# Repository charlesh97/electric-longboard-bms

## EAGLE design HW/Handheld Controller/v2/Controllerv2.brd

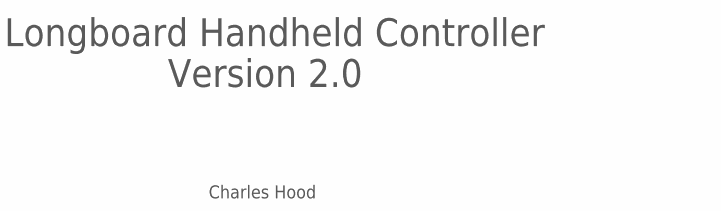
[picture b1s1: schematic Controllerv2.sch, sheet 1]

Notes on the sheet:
Longboard Handheld Controller
Version 2.0
Charles Hood

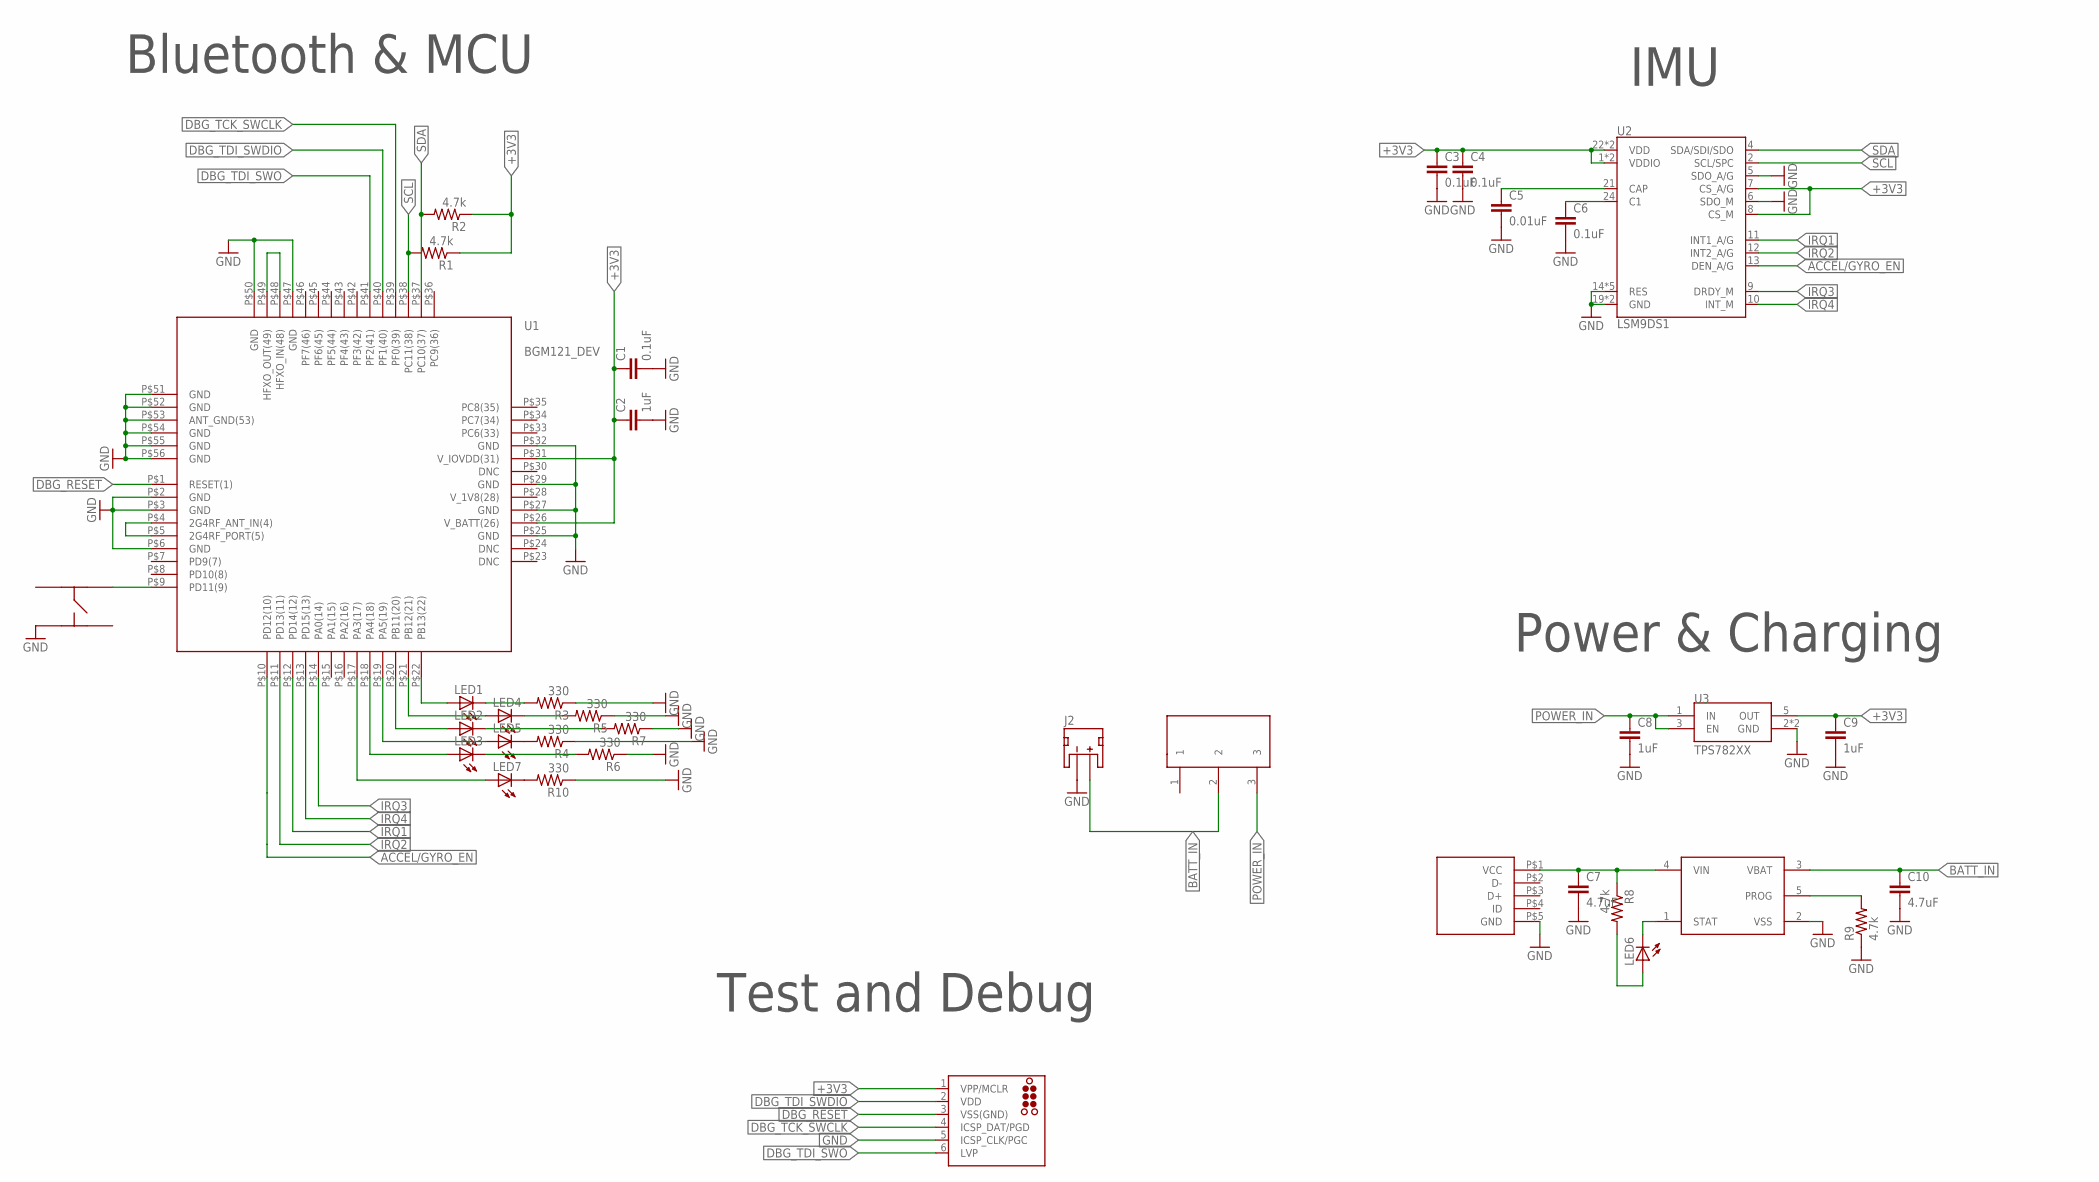
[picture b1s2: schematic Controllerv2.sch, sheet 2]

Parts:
C1, C3, C4, C6: 0.1uF; C0201
C2, C8, C9: 1uF; C0201
C5: 0.01uF; C0201
C7, C10: 4.7uF; C0402
J1: MICRO_USB; MOLEX_USB
J2: JST_2MM_MALE; JST-2-SMD
J3: TC2030-MCP-NL
LED1, LED2, LED3, LED4, LED5, LED6, LED7: LEDCHIP-LED0603; CHIP-LED0603
R1, R2, R8, R9: 4.7k; R0201
R3, R4, R5, R6, R7, R10: 330; R0201
S1: KMR731NG
U1: BGM121_DEV; BGM121_PAC
U2: LSM9DS1; LGA24-8X4
U3: TPS782XX; SOT23-5L
U4: MCP73831; SOT23-5L
U$1: SPDT_THRU

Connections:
+3V3: C1.1, C2.1, C3.1, C4.1, C9.1, J3.1 (VPP/MCLR), R1.1, R2.1, U1.P$26 (V_BATT(26)), U1.P$31 (V_IOVDD(31)), U2.1 (VDDIO), U2.3 (VDDIO), U2.7 (CS_A/G), U2.8 (CS_M), U2.22 (VDD), U2.23 (VDD), U3.5 (OUT)
ACCEL/GYRO_EN: U1.P$10 (PD12(10)), U2.13 (DEN_A/G)
BATT_IN: C10.1, J2.2 (+), U4.3 (VBAT), U$1.2
DBG_RESET: J3.3 (VSS(GND)), U1.P$1 (RESET(1))
DBG_TCK_SWCLK: J3.4 (ICSP_DAT/PGD), U1.P$39 (PF0(39))
DBG_TDI_SWDIO: J3.2 (VDD), U1.P$40 (PF1(40))
DBG_TDI_SWO: J3.6 (LVP), U1.P$41 (PF2(41))
GND: C1.2, C2.2, C3.2, C4.2, C5.2, C6.2, C7.2, C8.2, C9.2, C10.2, J1.P$5 (GND), J2.1 (-), J3.5 (ICSP_CLK/PGC), R3.1, R4.1, R5.1, R6.1, R7.1, R9.1, R10.1, S1.P$4, U1.P$2 (GND), U1.P$3 (GND), U1.P$6 (GND), U1.P$25 (GND), U1.P$27 (GND), U1.P$29 (GND), U1.P$32 (GND), U1.P$47 (GND), U1.P$50 (GND), U1.P$51 (GND), U1.P$52 (GND), U1.P$53 (ANT_GND(53)), U1.P$54 (GND), U1.P$55 (GND), U1.P$56 (GND), U2.5 (SDO_A/G), U2.6 (SDO_M), U2.14 (RES), U2.15 (RES), U2.16 (RES), U2.17 (RES), U2.18 (RES), U2.19 (GND), U2.20 (GND), U3.2 (GND), U3.4 (GND), U4.2 (VSS)
IRQ1: U1.P$12 (PD14(12)), U2.11 (INT1_A/G)
IRQ2: U1.P$11 (PD13(11)), U2.12 (INT2_A/G)
IRQ3: U1.P$14 (PA0(14)), U2.9 (DRDY_M)
IRQ4: U1.P$13 (PD15(13)), U2.10 (INT_M)
unnamed: LED1.A, U1.P$22 (PB13(22))
unnamed: LED4.A, U1.P$21 (PB12(21))
unnamed: LED2.A, U1.P$20 (PB11(20))
unnamed: LED5.A, U1.P$19 (PA5(19))
unnamed: LED3.C, R6.2
unnamed: LED3.A, U1.P$18 (PA4(18))
unnamed: C5.1, U2.21 (CAP)
unnamed: C6.1, U2.24 (C1)
unnamed: C7.1, J1.P$1 (VCC), R8.1, U4.4 (VIN)
unnamed: R9.2, U4.5 (PROG)
unnamed: LED6.A, R8.2
unnamed: LED6.C, U4.1 (STAT)
unnamed: S1.P$2, U1.P$9 (PD11(9))
unnamed: LED7.C, R10.2
unnamed: LED7.A, U1.P$17 (PA3(17))
unnamed: LED4.C, R5.2
unnamed: LED2.C, R7.2
unnamed: LED5.C, R4.2
unnamed: U1.P$4 (2G4RF_ANT_IN(4)), U1.P$5 (2G4RF_PORT(5))
unnamed: LED1.C, R3.2
unnamed: U1.P$48 (HFXO_IN(48)), U1.P$49 (HFXO_OUT(49))
POWER_IN: C8.1, U3.1 (IN), U3.3 (EN), U$1.3
SCL: R1.2, U1.P$38 (PC11(38)), U2.2 (SCL/SPC)
SDA: R2.2, U1.P$37 (PC10(37)), U2.4 (SDA/SDI/SDO)
V_1V8(28): U1.P$28 (V_1V8(28))

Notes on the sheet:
Bluetooth & MCU
IMU
Power & Charging
Test and Debug

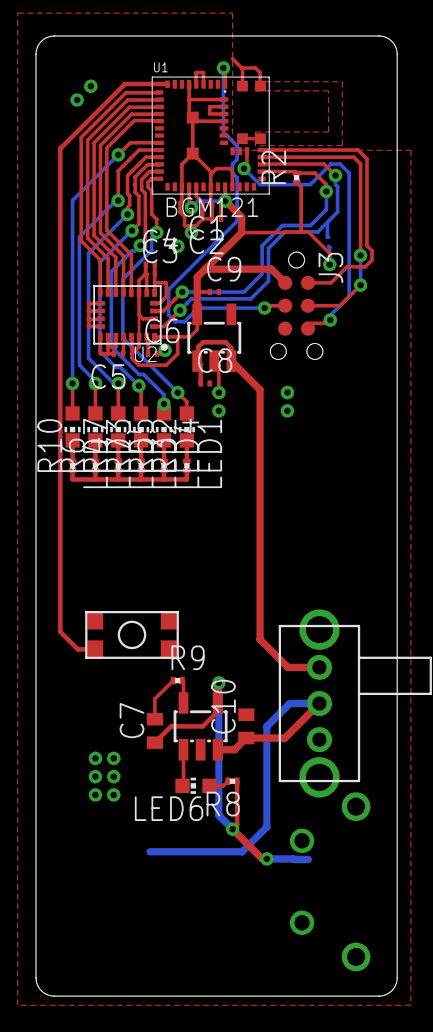
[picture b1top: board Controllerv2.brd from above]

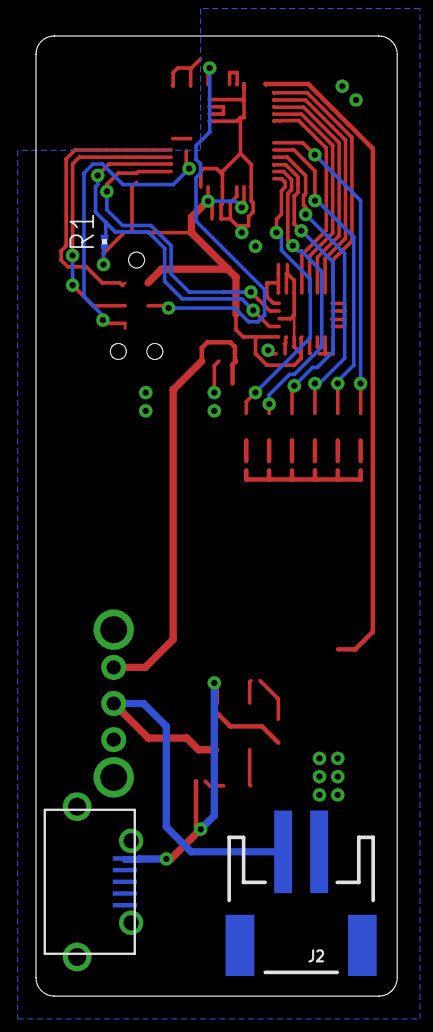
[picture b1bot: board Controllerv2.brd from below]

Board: 2 copper layers, 20.1 x 53.3 mm, 36 parts (3 on the bottom side), 36 nets.

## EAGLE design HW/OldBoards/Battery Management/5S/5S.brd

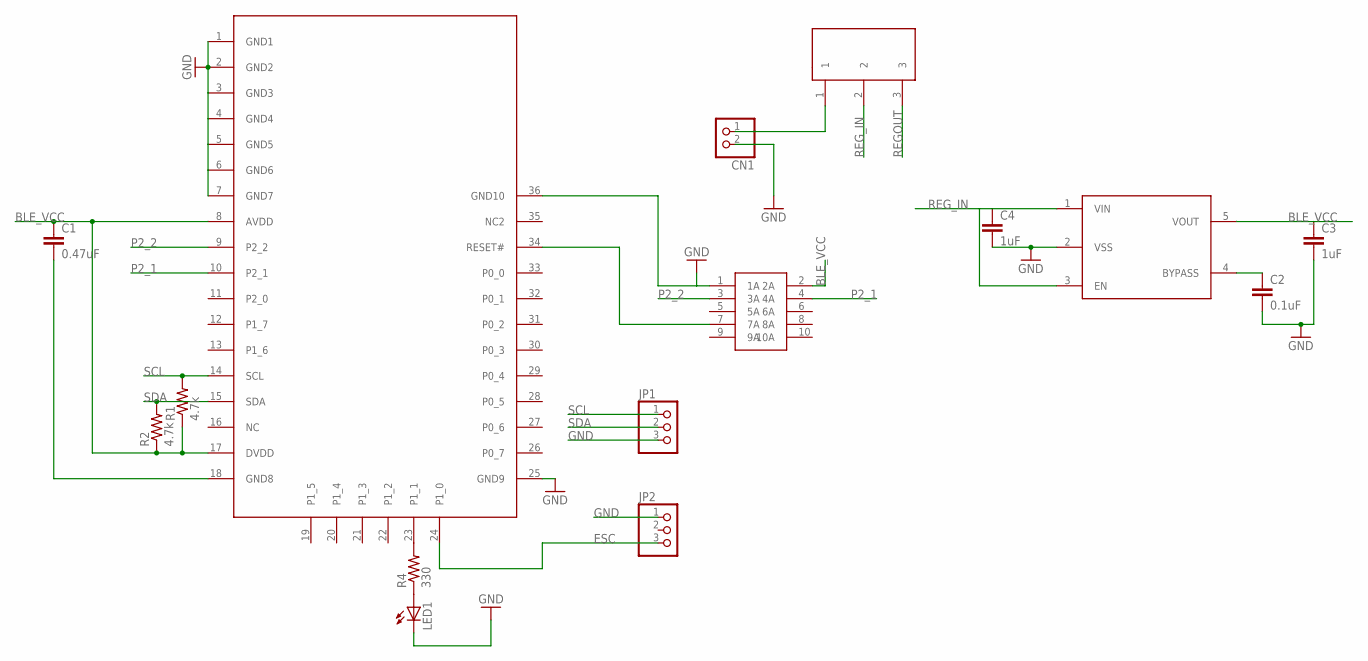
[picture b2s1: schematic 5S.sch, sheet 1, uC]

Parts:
C1: 0.47uF; C0402
C2: 0.1uF; C0402
C3, C4: 1uF; C0402
CN1: JST_2PIN-THM; JST-PH-2-THM
JP1, JP2: PINHD-1X3; 1X03
LED1: LEDCHIP-LED0805; CHIP-LED0805
R1, R2: 4.7k; R0402
R4: 330; R0402
U$1: BLE113; BLUEGIGA
U$2: RIBBON_10POS_MALE
U$4: SPDT_THRU
U$5: LP3985; SOT23-5L

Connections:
BLE_VCC: C1.1, C3.1, R1.1, R2.1, U$1.8 (AVDD), U$1.17 (DVDD), U$2.2 (2A), U$5.5 (VOUT)
ESC: JP2.3, U$1.24 (P1_0)
GND: C2.2, C3.2, C4.2, CN1.2 (1), JP1.3, JP2.1, LED1.C, U$1.1 (GND1), U$1.2 (GND2), U$1.3 (GND3), U$1.4 (GND4), U$1.5 (GND5), U$1.6 (GND6), U$1.7 (GND7), U$1.25 (GND9), U$1.36 (GND10), U$2.1 (1A), U$5.2 (VSS); also elsewhere on the board
unnamed: U$1.34 (RESET#), U$2.7 (7A)
unnamed: CN1.1 (2), U$4.1
unnamed: C1.2, U$1.18 (GND8)
unnamed: R4.2, U$1.23 (P1_1)
unnamed: C2.1, U$5.4 (BYPASS)
unnamed: LED1.A, R4.1
P2_1: U$1.10 (P2_1), U$2.4 (4A)
P2_2: U$1.9 (P2_2), U$2.3 (3A)
REGOUT: U$4.3; also elsewhere on the board
REG_IN: C4.1, U$4.2, U$5.1 (VIN), U$5.3 (EN)
SCL: JP1.1, R1.2, U$1.14 (SCL); also elsewhere on the board
SDA: JP1.2, R2.2, U$1.15 (SDA); also elsewhere on the board

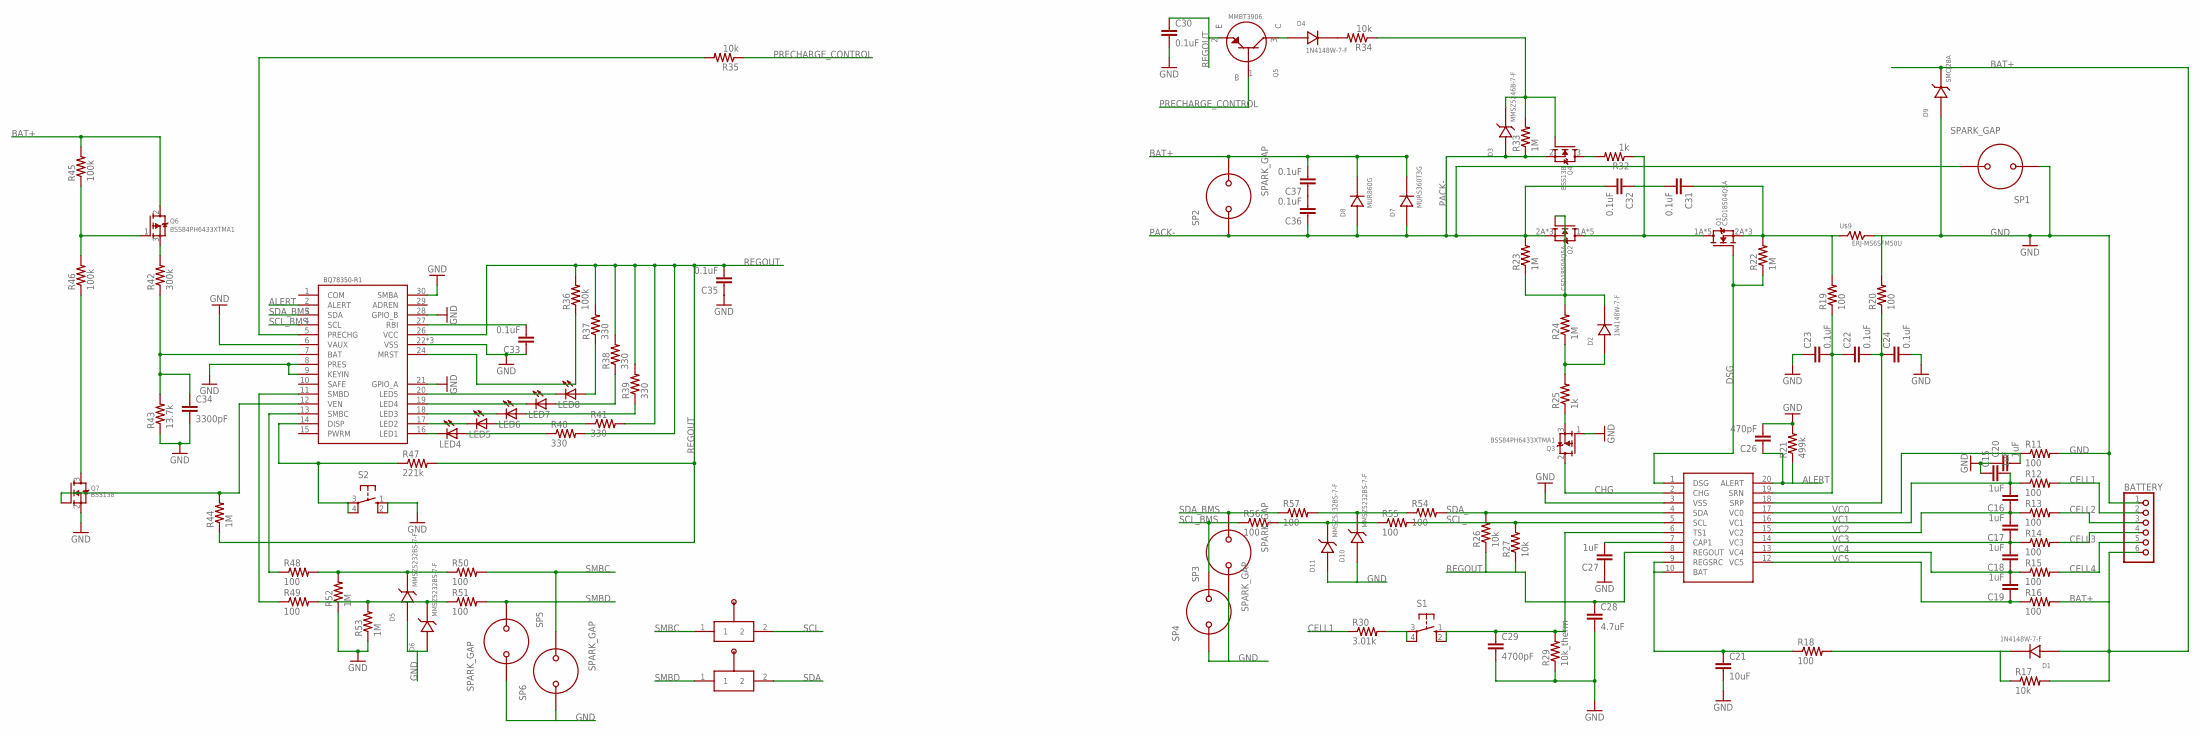
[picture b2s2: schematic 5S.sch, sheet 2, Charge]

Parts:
BATTERY: PINHD-1X6; 1X06
C15, C16, C17, C18, C19, C20, C27: 1uF; C0805
C21: 10uF; C1206
C22, C23, C24, C30, C31, C32, C33, C35, C36, C37: 0.1uF; C0805
C26: 470pF; C0805
C28: 4.7uF; C0805
C29: 4700pF; C0402
C34: 3300pF; C0402
D1, D2, D4: 1N4148W-7-F; SOD-123
D3: MMSZ5246B-7-F; SOD-123
D5, D6, D10, D11: MMSZ5232BS-7-F; SOD-323F
D7: MURS360T3G; SMC(DO-214AB)
D8: MUR860G; TO-220(2RA)
D9: SMCJ28A; SMC(DO-214AB)
LED4, LED5, LED6, LED7, LED8: LEDCHIPLED_0805; CHIPLED_0805
Q1, Q2: CSD18504Q5A; Q5A
Q3, Q6: BSS84PH6433XTMA1; SOT23-3
Q4, Q7: BSS138; SOT23-3
Q5: MMBT3906; SOT23-3
R11, R12, R13, R14, R15, R16: 100; R1206
R17, R26, R27, R34, R35: 10k; R0805
R18, R19, R20, R48, R49, R50, R51, R54, R55, R56, R57: 100; R0805
R21: 499k; R0805
R22, R23, R24, R33, R44, R52, R53: 1M; R1206
R25: 1k; R0805
R29: 10k_therm; R0402
R30: 3.01k; R0805
R32: 1k; R2512
R36, R45, R46: 100k; R0805
R37, R38, R39, R40, R41: 330; R0402
R42: 300k; R0805
R43: 13.7k; R0805
R47: 221k; R0805
S1, S2: 10-XX; B3F-10XX
SP1, SP2, SP3, SP4, SP5, SP6: SPARK_GAP
U$3: BQ76920; SOIC-20
U$9: ERJ-MS6SFM50U
U$10: BQ78350-R1; SOIC-30
U$16, U$17: MANUAL_SWITCH

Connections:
ALERT: C26.1, R21.1, U$3.20 (ALERT), U$10.2 (ALERT)
BAT+: BATTERY.6, C37.2, D1.P$1, D7.2, D8.P$3, D9.2, Q6.2 (S), R16.2, R17.2, R45.2, SP2.P$2
CELL1: BATTERY.2, R12.2, R30.1
CELL2: BATTERY.3, R13.2
CELL3: BATTERY.4, R14.2
CELL4: BATTERY.5, R15.2
CHG: Q3.2 (S), U$3.2 (CHG)
DSG: Q1.3A (G), R22.1, U$3.1 (DSG)
GND: BATTERY.1, C15.1, C20.1, C21.2, C23.1, C24.2, C26.2, C27.1, C28.2, C29.2, C30.2, C33.1, C34.2, C35.1, D5.1, D6.1, D9.1, D10.1, D11.1, Q3.1 (G), Q7.2 (S), R11.2, R20.2, R21.2, R29.1, R43.1, R52.1, R53.1, S2.1 (S), S2.2 (S1), SP1.P$1, SP3.P$1, SP4.P$1, SP5.P$2, SP6.P$1, U$3.3 (VSS), U$9.2, U$10.6 (VAUX), U$10.8 (PRES), U$10.9 (KEYIN), U$10.21 (GPIO_A), U$10.22 (VSS), U$10.23 (VSS), U$10.25 (VSS), U$10.28 (GPIO_B), U$10.30 (SMBA); also elsewhere on the board
unnamed: C21.1, R18.1, U$3.9 (REGSRC), U$3.10 (BAT)
unnamed: C22.2, C24.1, R20.1, U$3.18 (SRP)
unnamed: D1.P$2, R17.1, R18.2
unnamed: D11.2, R55.1, R56.2
unnamed: C31.1, Q1.2A (S), Q1.2B (S), Q1.2C (S), R19.2, R22.2, U$9.1
unnamed: C22.1, C23.2, R19.1, U$3.19 (SRN)
unnamed: C27.2, U$3.7 (CAP1)
unnamed: Q4.3 (D), R32.2
unnamed: D4.P$2, R34.2
unnamed: D3.P$2 (2), Q4.1 (G), R33.2, R34.1
unnamed: D4.P$1, Q5.3 (C)
unnamed: D2.P$1, R24.1, R25.2
unnamed: Q1.1A (D), Q1.1B (D), Q1.1C (D), Q1.1D (D), Q1.1E (D), Q2.1A (D), Q2.1B (D), Q2.1C (D), Q2.1D (D), Q2.1E (D), R32.1
unnamed: C36.2, C37.1
unnamed: D2.P$2, Q2.3A (G), R23.1, R24.2
unnamed: Q3.3 (D), R25.1
unnamed: R30.2, S1.3, S1.4 (P1)
unnamed: C29.1, R29.2, S1.1 (S), S1.2 (S1), U$3.6 (TS1)
unnamed: C31.2, C32.1
unnamed: C33.2, U$10.27 (RBI)
unnamed: R35.2, U$10.5 (PRECHG)
unnamed: R36.1, U$10.24 (MRST)
unnamed: Q7.3 (D), R46.1
unnamed: LED8.C, U$10.20 (LED5)
unnamed: LED7.C, U$10.19 (LED4)
unnamed: LED6.C, U$10.18 (LED3)
unnamed: LED5.C, U$10.17 (LED2)
unnamed: LED4.C, U$10.16 (LED1)
unnamed: LED4.A, R40.1
unnamed: LED5.A, R41.1
unnamed: LED6.A, R39.1
unnamed: LED7.A, R38.1
unnamed: LED8.A, R37.1
unnamed: C34.1, R42.1, R43.2, U$10.7 (BAT)
unnamed: Q7.1 (G), R44.2, U$10.12 (VEN)
unnamed: Q6.3 (D), R42.2
unnamed: Q6.1 (G), R45.1, R46.2
unnamed: R48.1, U$10.13 (SMBC)
unnamed: R47.1, S2.3, S2.4 (P1), U$10.14 (DISP)
unnamed: R49.1, U$10.11 (SMBD)
unnamed: D5.2, R48.2, R50.1, R52.2
unnamed: D6.2, R49.2, R51.1, R53.2
unnamed: D10.2, R54.1, R57.2
PACK-: C32.2, C36.1, D3.P$1 (1), D7.1, D8.P$1, Q2.2A (S), Q2.2B (S), Q2.2C (S), Q4.2 (S), R23.2, R33.1, SP1.P$2, SP2.P$1
PRECHARGE_CONTROL: Q5.1 (B), R35.1
REGOUT: C28.1, C30.1, C35.2, Q5.2 (E), R26.1, R27.1, R36.2, R37.2, R38.2, R39.2, R40.2, R41.2, R44.1, R47.2, U$3.8 (REGOUT), U$10.26 (VCC); also elsewhere on the board
SCL: U$16.2; also elsewhere on the board
SCL_: R27.2, R55.2, U$3.5 (SCL)
SCL_BMS: R56.1, SP4.P$2, U$10.4 (SCL)
SDA: U$17.2; also elsewhere on the board
SDA_: R26.2, R54.2, U$3.4 (SDA)
SDA_BMS: R57.1, SP3.P$2, U$10.3 (SDA)
SMBC: R50.2, SP6.P$2, U$16.1
SMBD: R51.2, SP5.P$1, U$17.1
VC0: C20.2, R11.1, U$3.17 (VC0)
VC1: C15.2, C16.2, R12.1, U$3.16 (VC1)
VC2: C16.1, C17.2, R13.1, U$3.15 (VC2)
VC3: C17.1, C18.2, R14.1, U$3.14 (VC3)
VC4: C18.1, C19.2, R15.1, U$3.13 (VC4)
VC5: C19.1, R16.1, U$3.12 (VC5)

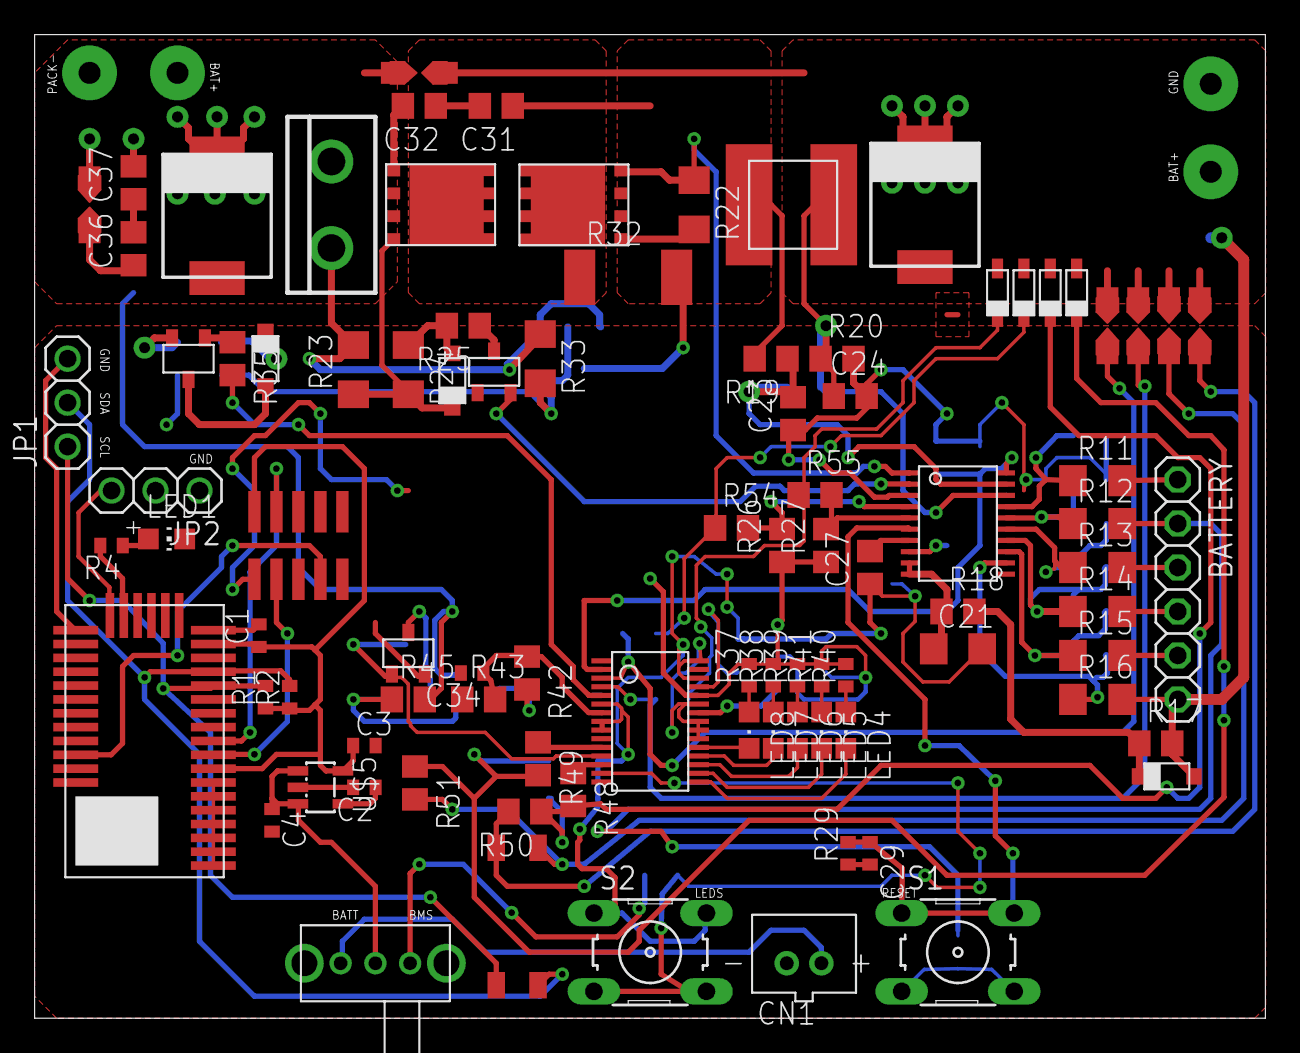
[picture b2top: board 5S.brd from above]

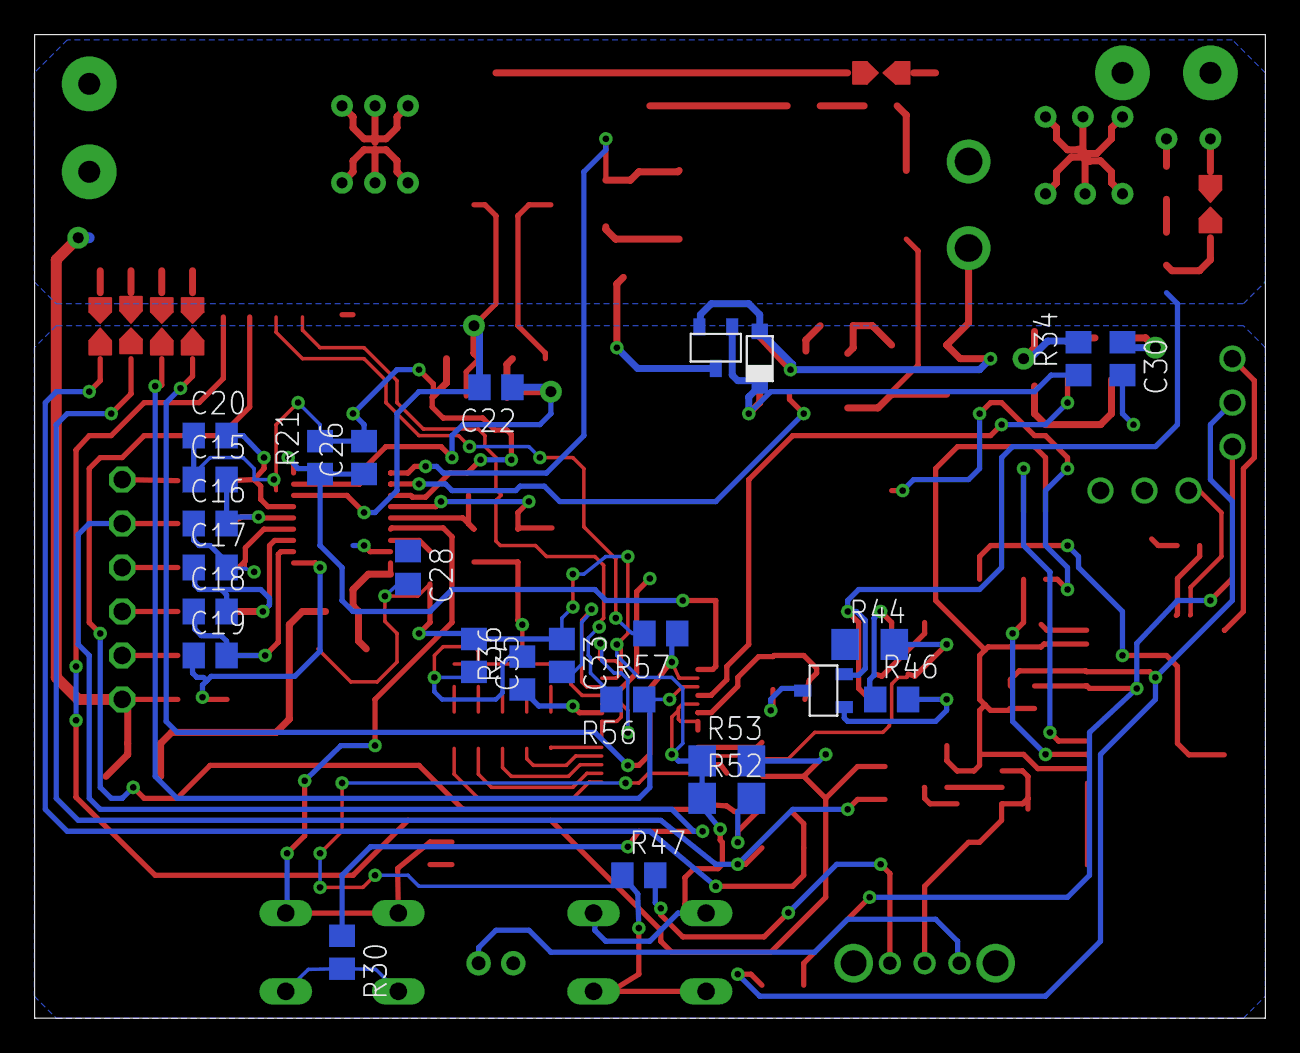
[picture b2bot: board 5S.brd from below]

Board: 2 copper layers, 71.1 x 56.8 mm, 119 parts (26 on the bottom side), 80 nets.

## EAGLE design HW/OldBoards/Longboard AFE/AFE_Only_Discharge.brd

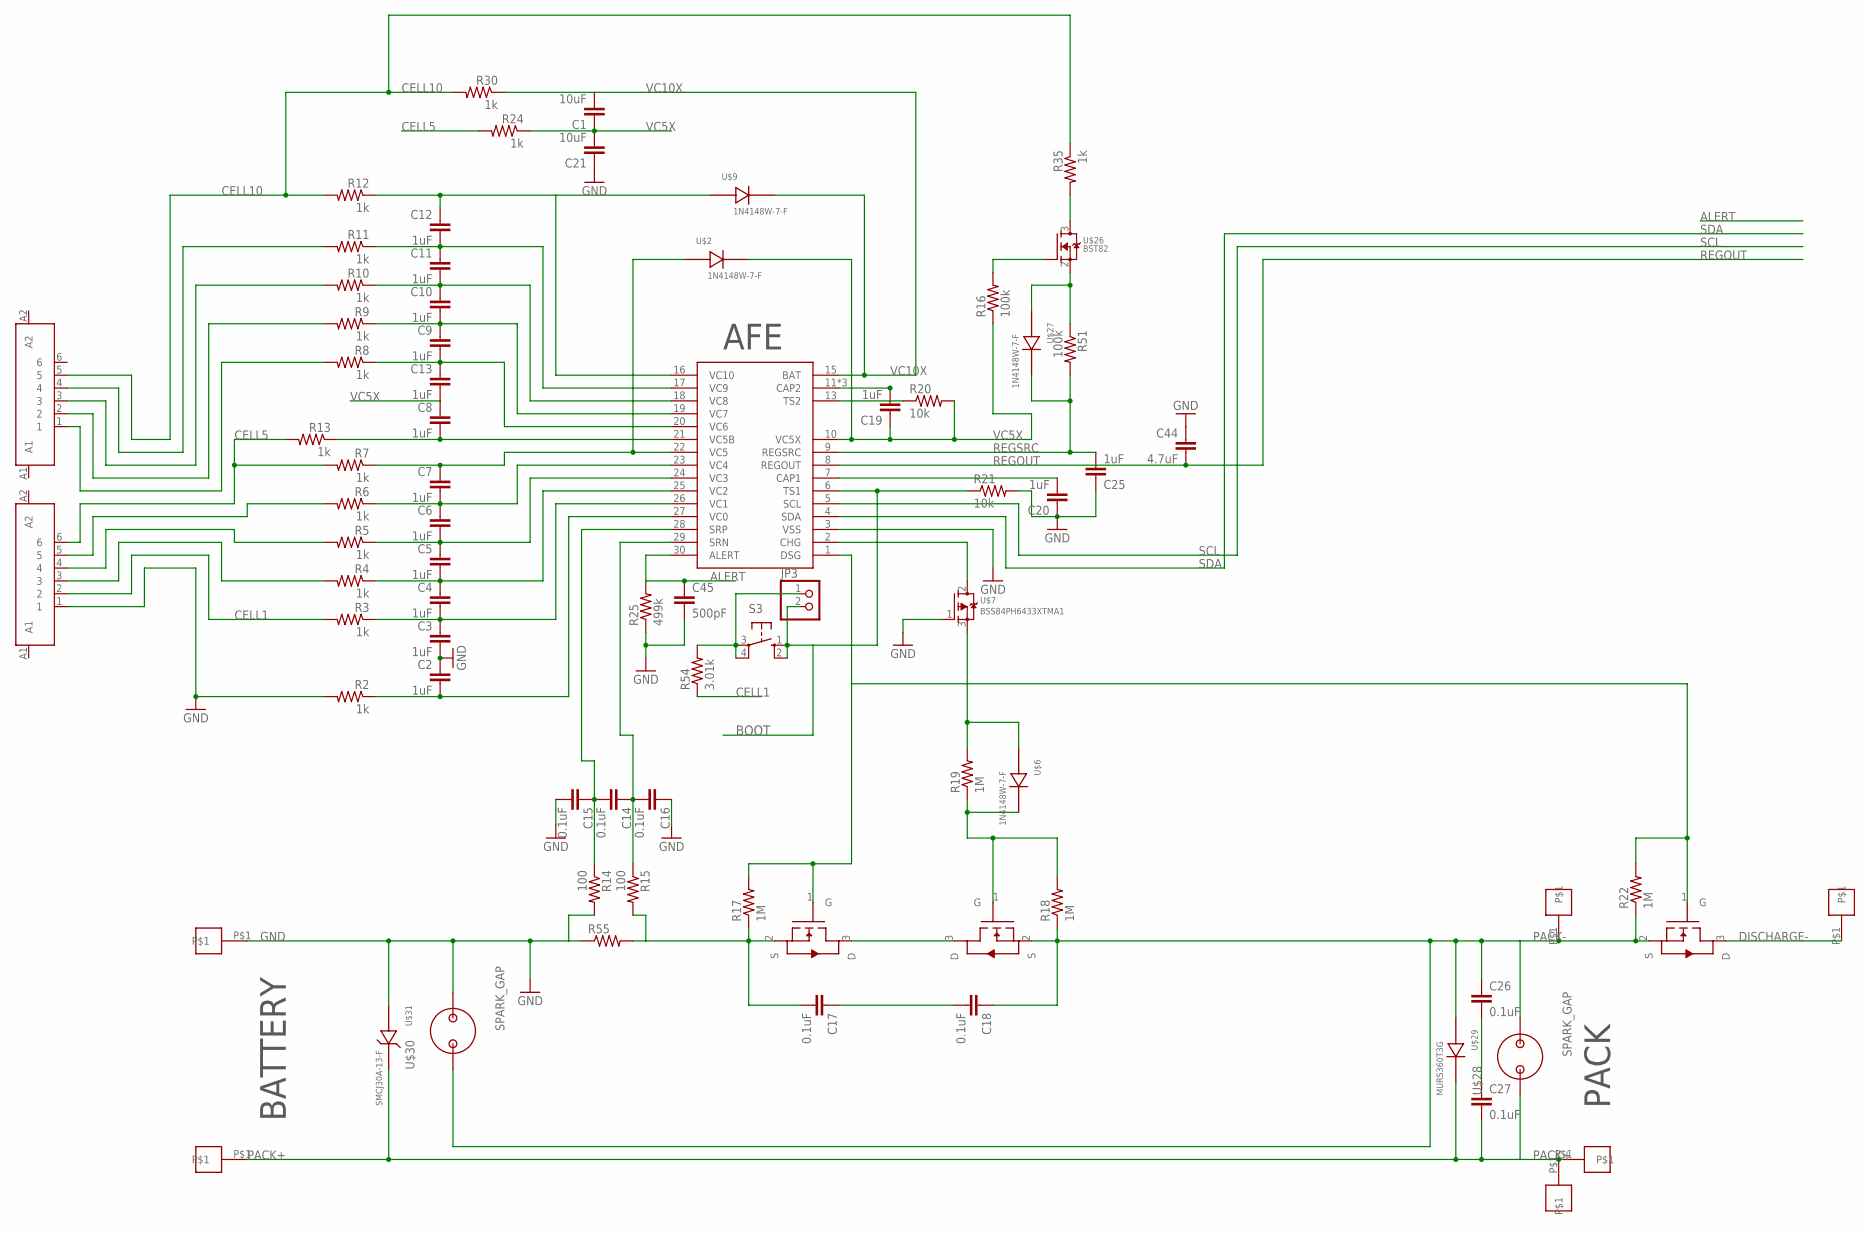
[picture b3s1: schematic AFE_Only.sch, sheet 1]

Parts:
C1, C21: 10uF; C1210
C2, C3, C4, C5, C6, C7, C8, C9, C10, C11, C12, C13, C19, C20, C25: 1uF; C0805
C14, C15, C16, C17, C18, C26, C27: 0.1uF; C0805
C44: 4.7uF; C0805
C45: 500pF; C0603
JP3: PINHD-1X2; 1X02
R2, R3, R4, R5, R6, R7, R8, R9, R10, R11, R12, R13, R24, R30, R35: 1k; R1206
R14, R15: 100; R0805
R16, R51: 100k; R0805
R17, R18, R19, R22: 1M; R1206
R20, R21: 10k; R0805
R25: 499k; R0603
R54: 3.01k; R1206
R55: R-US_R2512; R2512
S3: 10-XX; B3F-10XX
U$1: BQ76930; SOIC-30
U$2, U$6, U$9, U$27: 1N4148W-7-F; SOD-123
U$3, U$35, U$36, U$37, U$38, U$39: PAD
U$4, U$5, U$10: AOB290L; TO-263
U$7: BSS84PH6433XTMA1; SOT23-3
U$24, U$33: JST_6PIN
U$26: BST82; SOT23-3
U$28, U$30: SPARK_GAP
U$29: MURS360T3G; SMC(DO-214AB)
U$31: SMCJ30A-13-F; SMB(DO-214AA)

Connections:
ALERT: C45.1, R25.2, U$1.30 (ALERT); also elsewhere on the board
BOOT: JP3.2, R21.1, S3.1 (S), S3.2 (S1), U$1.6 (TS1)
CELL1: R3.2, R54.1, U$33.2
CELL5: R7.2, R13.2, R24.2, U$33.6
CELL10: R12.2, R30.2, R35.1, U$24.5
GND: C2.1, C3.2, C15.2, C16.1, C20.1, C21.1, C25.1, C44.1, C45.2, R2.2, R14.2, R21.2, R25.1, R55.1, U$1.3 (VSS), U$3.P$1, U$7.1 (G), U$30.P$2, U$31.P$1 (1), U$33.1; also elsewhere on the board
unnamed: C3.1, C4.2, R3.1, U$1.26 (VC1)
unnamed: C4.1, C5.2, R4.1, U$1.25 (VC2)
unnamed: C5.1, C6.2, R5.1, U$1.24 (VC3)
unnamed: C6.1, C7.2, R6.1, U$1.23 (VC4)
unnamed: C7.1, R7.1, U$1.22 (VC5), U$2.P$1
unnamed: C8.2, R13.1, U$1.21 (VC5B)
unnamed: C9.1, C10.2, R9.1, U$1.19 (VC7)
unnamed: C10.1, C11.2, R10.1, U$1.18 (VC8)
unnamed: C11.1, C12.2, R11.1, U$1.17 (VC9)
unnamed: C12.1, R12.1, U$1.16 (VC10), U$9.P$1
unnamed: R5.2, U$33.4
unnamed: C2.2, R2.1, U$1.27 (VC0)
unnamed: C26.2, C27.1
unnamed: R4.2, U$33.3
unnamed: R6.2, U$33.5
unnamed: R8.2, U$24.1
unnamed: R9.2, U$24.2
unnamed: R10.2, U$24.3
unnamed: R11.2, U$24.4
unnamed: C9.2, C13.1, R8.1, U$1.20 (VC6)
unnamed: R16.2, U$26.1 (G)
unnamed: C20.2, U$1.7 (CAP1)
unnamed: C14.1, C16.2, R15.1, U$1.29 (SRN)
unnamed: JP3.1, R54.2, S3.3, S3.4 (P1)
unnamed: C14.2, C15.1, R14.1, U$1.28 (SRP)
unnamed: R18.2, R19.1, U$5.1 (G), U$6.P$2
unnamed: R19.2, U$6.P$1, U$7.3 (D)
unnamed: U$1.2 (CHG), U$7.2 (S)
unnamed: C17.1, C18.2
unnamed: C19.2, U$1.11 (CAP2), U$1.12 (CAP2), U$1.14 (CAP2)
unnamed: R20.1, U$1.13 (TS2)
unnamed: R51.1, U$26.2 (S), U$27.P$1
unnamed: R35.2, U$26.3 (D)
PACK+: C27.2, U$28.P$1, U$29.2, U$31.P$2 (2), U$35.P$1, U$36.P$1, U$39.P$1
REGOUT: C44.2, U$1.8 (REGOUT); also elsewhere on the board
REGSRC: C25.2, R51.2, U$1.9 (REGSRC), U$27.P$2
SCL: U$1.5 (SCL); also elsewhere on the board
SDA: U$1.4 (SDA); also elsewhere on the board
VC5X: C1.1, C8.1, C13.2, C19.1, C21.2, R16.1, R20.2, R24.1, U$1.10 (VC5X), U$2.P$2
VC10X: C1.2, R30.1, U$1.15 (BAT), U$9.P$2

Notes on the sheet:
BATTERY
PACK
AFE

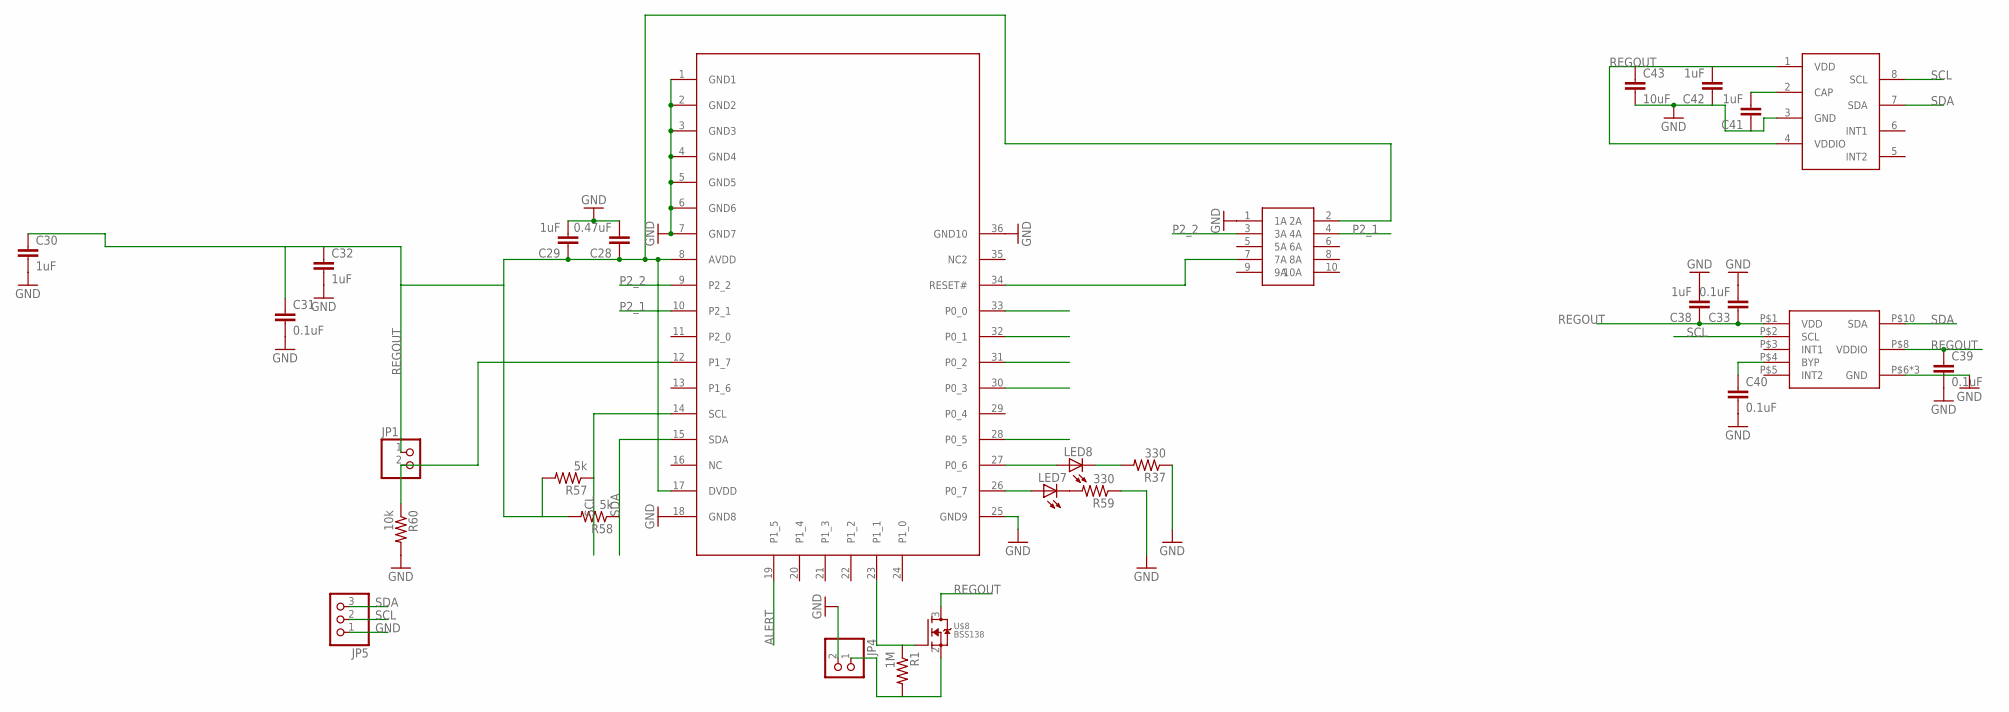
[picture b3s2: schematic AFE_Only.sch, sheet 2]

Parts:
C28: 0.47uF; C0402
C29, C30, C32, C38, C41, C42: 1uF; C0402
C31, C33, C39, C40: 0.1uF; C0402
C43: 10uF; C0603
JP1, JP4: PINHD-1X2; 1X02
JP5: PINHD-1X3; 1X03
LED7, LED8: LEDCHIP-LED0603; CHIP-LED0603
R1: 1M; R0402
R37, R59: 330; R0402
R57, R58: 5k; R0402
R60: 10k; R0402
U$8: BSS138; SOT23-3
U$20: BLE113; BLUEGIGA
U$22: RIBBON_10POS_MALE
U$25: MLP3115A2
U$32: MMA8653FC; 10-DFN2X2

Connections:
ALERT: U$20.19 (P1_5); also elsewhere on the board
CARD2: U$20.32 (P0_1)
CD: U$20.33 (P0_0)
CLK: U$20.28 (P0_5)
GND: C28.2, C29.2, C30.2, C31.2, C32.2, C33.2, C38.2, C39.2, C40.2, C41.1, C42.1, C43.2, JP4.2, JP5.1, R37.1, R59.1, R60.2, U$20.1 (GND1), U$20.2 (GND2), U$20.3 (GND3), U$20.4 (GND4), U$20.5 (GND5), U$20.6 (GND6), U$20.7 (GND7), U$20.18 (GND8), U$20.25 (GND9), U$20.36 (GND10), U$22.1 (1A), U$25.3 (GND), U$32.P$6 (GND), U$32.P$7 (GND), U$32.P$9 (GND); also elsewhere on the board
MISO: U$20.31 (P0_2)
MOSI: U$20.30 (P0_3)
unnamed: LED8.A, U$20.27 (P0_6)
unnamed: LED8.C, R37.2
unnamed: LED7.A, U$20.26 (P0_7)
unnamed: JP1.2, R60.1, U$20.12 (P1_7)
unnamed: LED7.C, R59.2
unnamed: U$20.34 (RESET#), U$22.7 (7A)
unnamed: C41.2, U$25.2 (CAP)
unnamed: C40.1, U$32.P$4 (BYP)
P2_1: U$20.10 (P2_1), U$22.4 (4A)
P2_2: U$20.9 (P2_2), U$22.3 (3A)
REGOUT: C28.1, C29.1, C30.1, C31.1, C32.1, C33.1, C38.1, C39.1, C42.2, C43.1, JP1.1, R57.2, R58.2, U$8.3 (D), U$20.8 (AVDD), U$20.17 (DVDD), U$22.2 (2A), U$25.1 (VDD), U$25.4 (VDDIO), U$32.P$1 (VDD), U$32.P$8 (VDDIO); also elsewhere on the board
SCL: JP5.2, R57.1, U$20.14 (SCL), U$25.8 (SCL), U$32.P$2 (SCL); also elsewhere on the board
SDA: JP5.3, R58.1, U$20.15 (SDA), U$25.7 (SDA), U$32.P$10 (SDA); also elsewhere on the board

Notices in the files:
parts and their libraries:
SparkFun-Connectors: Licensing: Creative Commons ShareAlike 4.0 International - https://creativecommons.org/licenses/by-sa/4.0
Tag-Connect-Footprints: ©2009 ROFA.cz - modified and updated by Robert Darlington ‹rdarlington@gmail.com›
